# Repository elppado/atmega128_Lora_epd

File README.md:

# Atmega128_Lora_epd  wire-less Chat
## [ LoRa와 ePaper를 사용한 AVR 기반 저전력 다용도 통신 단말 ]

### 🚀 프로젝트 소개
------
atmega128과 Lora 모듈, 전자잉크 디스플레이를 사용하여 무선 채팅기 개발

### 🕰️ 개발 기간
------
* 22.07 ~ 22.09

### 📋 개발내용
------
- [Schematic](https://github.com/elppado/atmega128_Lora_epd/tree/main/PCB)
- [F/W](https://github.com/elppado/atmega128_Lora_epd/tree/main/firmware)  

### ⚙️ 개발환경
-----
* C
* **Tool** : xcode(avrdude_cross compile), kicad, fusion360

### 📋 BOM
------
Lora : NMT-UD434R0

Display : 2.13 inch EInk e-paper Display 250*122

Keypad : Q10

This project is licensed under the terms of the MIT license.

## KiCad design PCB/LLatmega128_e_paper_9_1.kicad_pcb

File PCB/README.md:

# PCB
-------

- atmega128a
- LoRa Module
- e-ink display

### Schematic

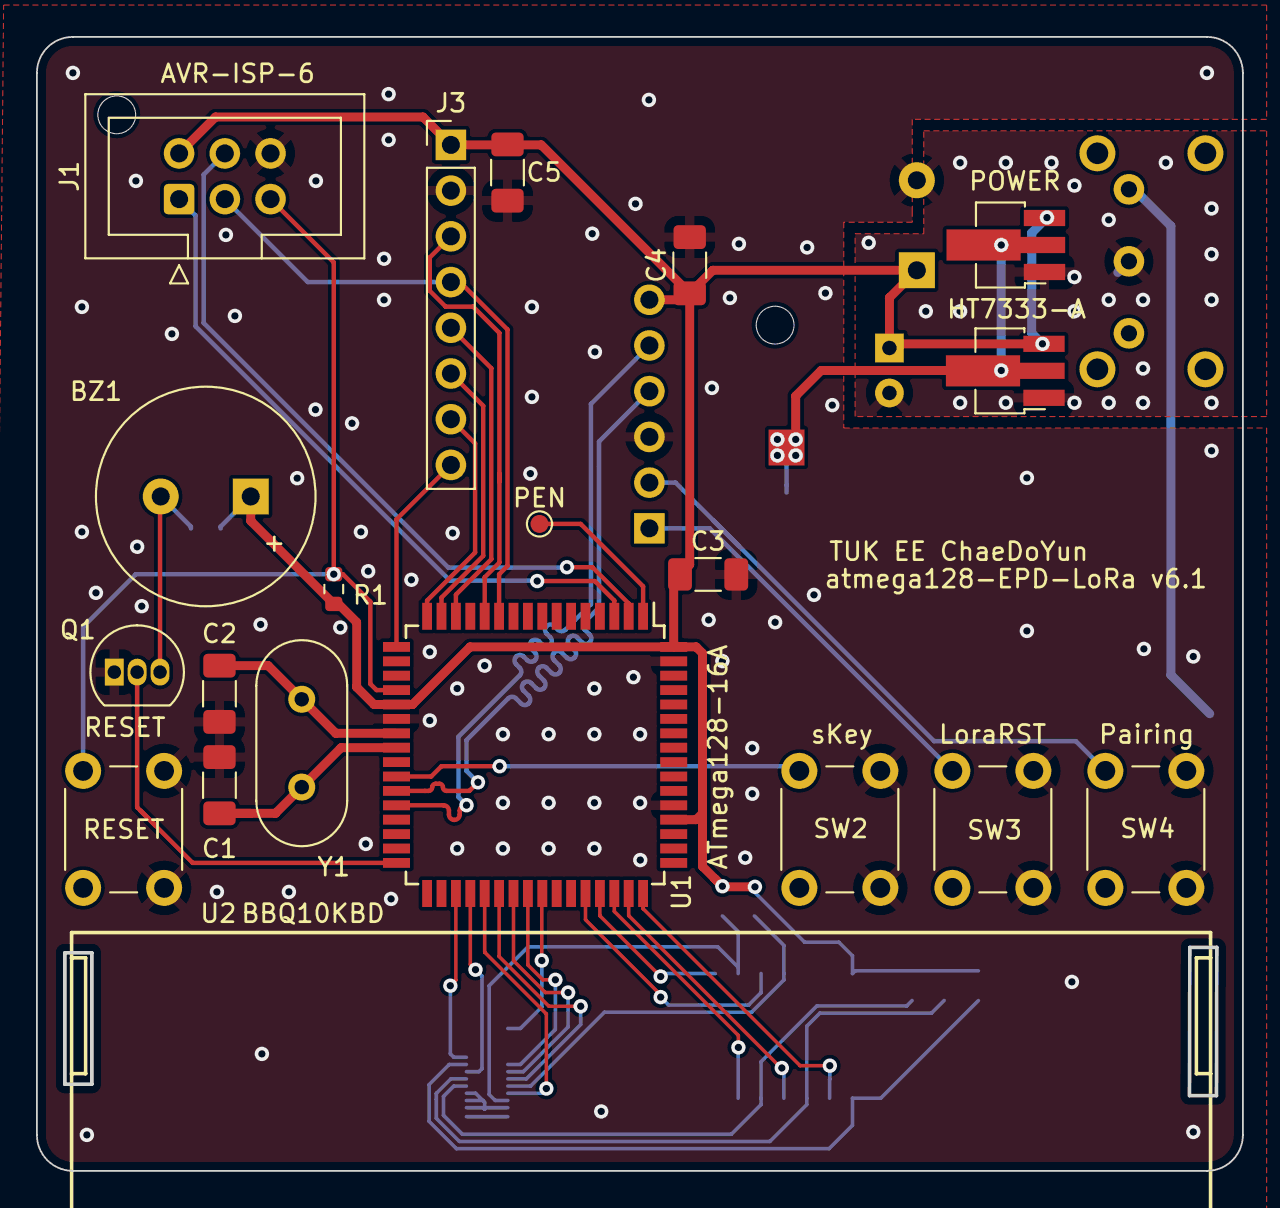
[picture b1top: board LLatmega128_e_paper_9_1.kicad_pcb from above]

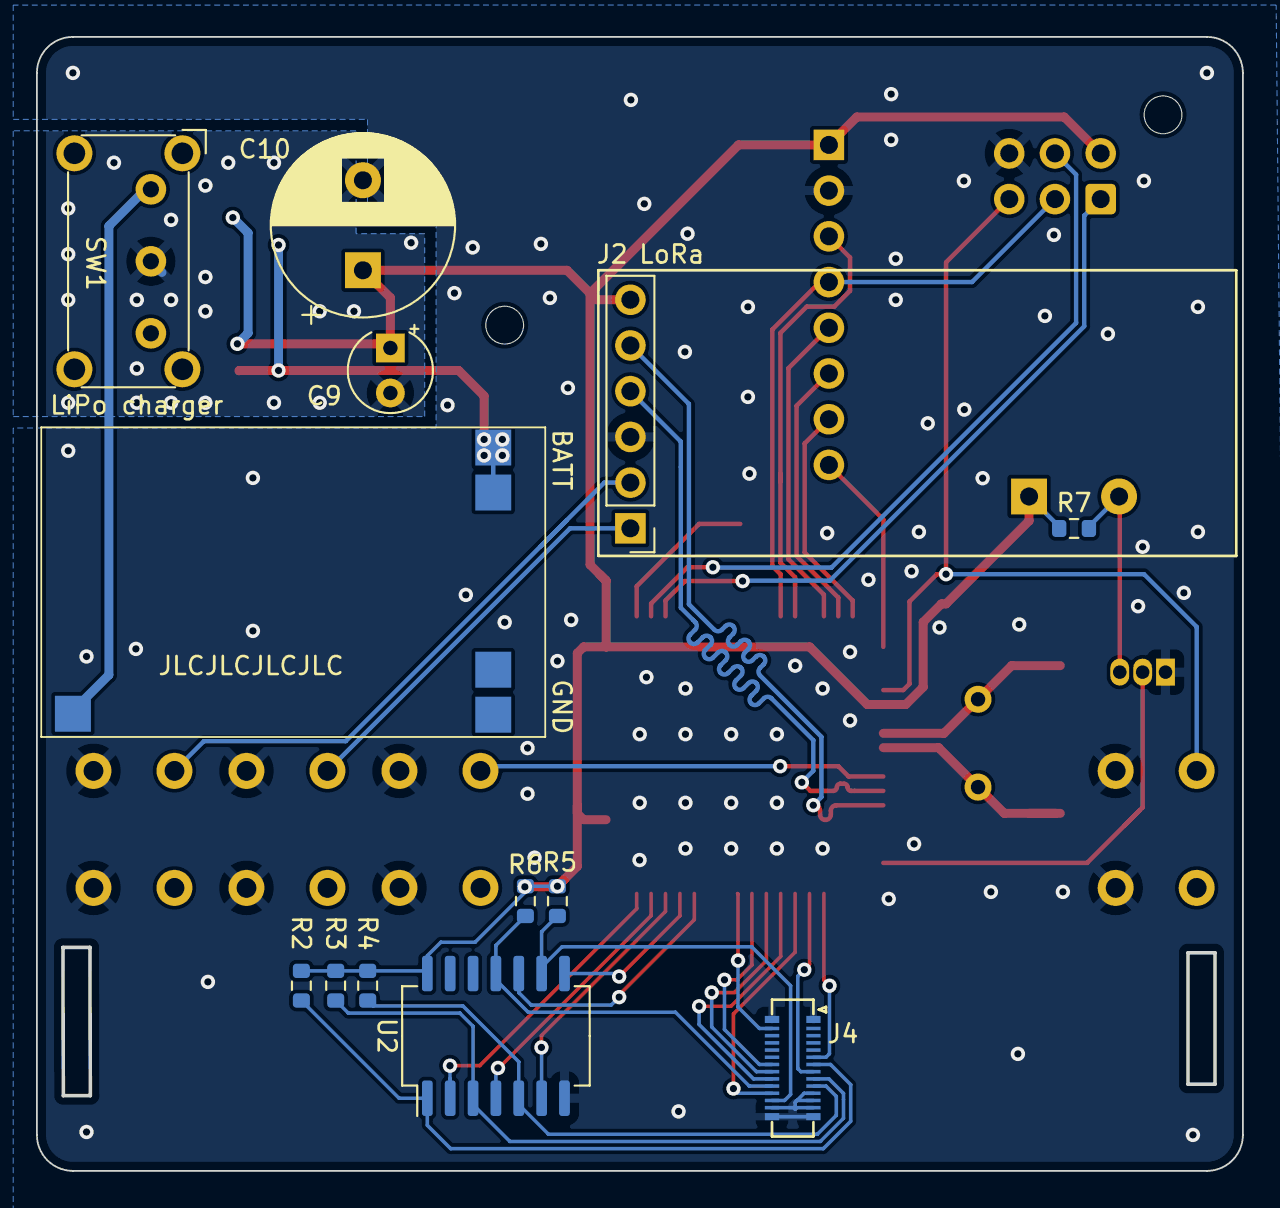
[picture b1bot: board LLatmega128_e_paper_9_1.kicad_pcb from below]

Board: 2 copper layers, 66.9 x 62.9 mm, 32 parts (12 on the bottom side), 38 nets.

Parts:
BZ1: Buzzer; Buzzer_12x9.5RM7.6
C1, C2: C22pF; C_1206_3216Metric_Pad1.33x1.80mm_HandSolder
C3, C4, C5: C_1206_3216Metric_Pad1.33x1.80mm_HandSolder
C9: CP_Radial_Tantal_D4.5mm_P2.50mm
C10: CP_Radial_D10.0mm_P5.00mm
J1: AVR-ISP-6; IDC-Header_2x03_P2.54mm_Vertical
J2: Conn_01x06_Male; PinHeader_1x06_P2.54mm_Vertical
J3: ePaper; PinHeader_1x08_P2.54mm_Vertical
J4: Conn_02x14_Counter_Clockwise; Hirose_BM14-24DS-2DSA_2x14_P2.00mm_Vertical
L1, L1#2: HT7333-A; SOT-89-3_Handsoldering
PEN: TestPoint_Pad_D1.0mm
POWER: SW_E-Switch_EG1224_SPDT_Angled
Q1: PN2222A; TO-92_Inline
R1: R10k; R_0603_1608Metric
R2, R3, R4, R5, R6, R7: R; R_0603_1608Metric
SW1, SW2, SW3, SW4: SW_Push; SW_PUSH_6mm_H4.3mm
U1: ATmega128-16A; TQFP-64_14x14mm_P0.8mm
U2: BBQ10KBD; Reverb_BTDR-1A
U2#2: 74HC14; SO-14_5.3x10.2mm_P1.27mm
Y1: Crystal; Crystal_HC49-4H_Vertical

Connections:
+3V3: BZ1.1 (-), C3.1, C4.1, C5.1, C9.1, C10.1, J1.2 (VCC), J2.6, J3.1, L1.3 (VOUT), L1#2.3 (VOUT), R1.1, R2.1, R3.1, R4.1, R5.1, R6.1, R7.1, U1.21 (VCC), U1.52 (VCC), U1.64 (AVCC), U2#2.14 (VCC)
-BATT: L1.2 (VIN), L1#2.2 (VIN)
/BUSY: J3.8, U1.17 (PB7)
/BUZZ: Q1.2 (B), U1.32 (PD7)
/COL1: U1.48 (PA3), U2#2.2
/COL2: U1.47 (PA4), U2#2.4
/COL3: U1.46 (PA5), U2#2.6
/COL4: U1.45 (PA6), U2#2.8
/COL5: U1.44 (PA7), U2#2.10
/CS: J3.5, U1.14 (PB4)
/D/C: J3.6, U1.15 (PB5)
/KCOL1: J4.7, R2.2, U2#2.1
/KCOL2: J4.9, R3.2, U2#2.3
/KCOL3: J4.10, R4.2, U2#2.5
/KCOL4: J4.17, R5.2, U2#2.9
/KCOL5: J4.19, R6.2, U2#2.11
/LoraRST: J2.1, SW3.2
/PIO6: J2.2, SW4.2
/RES: J3.7, U1.16 (PB6)
/ROW1: J4.6, U1.35 (PC0)
/ROW2: J4.8, U1.36 (PC1)
/ROW3: J4.18, U1.37 (PC2)
/ROW4: J4.20, U1.38 (PC3)
/ROW5: J4.21, U1.39 (PC4)
/ROW6: J4.22, U1.40 (PC5)
/ROW7: J4.27, U1.41 (PC6)
/RST: J1.5 (~RST), R1.2, SW1.2, U1.20 (~RESET)
/RXD0: J1.4 (MOSI), U1.2 (PE0)
/RXD1: J2.4, U1.27 (PD2)
/SCK: J1.3 (SCK), J3.4, U1.11 (PB1)
/SDI: J3.3, U1.12 (PB2)
/TXD0: J1.1 (MISO), U1.3 (PE1)
/TXD1: J2.5, U1.28 (PD3)
/X1: C1.2, U1.24 (XTAL1), Y1.2
/X2: C2.1, U1.23 (XTAL2), Y1.1
/sKEY: SW2.2, U1.26 (PD1)
GND: C1.1, C2.2, C3.2, C4.2, C5.2, C9.2, C10.2, J1.6 (GND), J2.3, J3.2, J4.1, J4.4, J4.5, J4.11, J4.12, J4.13, J4.14, J4.15, J4.16, J4.28, L1.1 (GND), L1#2.1 (GND), POWER.2, Q1.1 (E), SW1.1, SW2.1, SW3.1, SW4.1, U1.22 (GND), U1.53 (GND), U1.63 (GND), U2#2.7 (GND)
unnamed: BZ1.2 (+), Q1.3 (C), R7.2

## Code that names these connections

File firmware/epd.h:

/*
 * epd.h
 *
 * Created: 2022-07-17 오후 1:14:07
 *  Author: chaedoyun
 */ 


#ifndef EPD_H_
#define EPD_H_


#define SCK_Pin PB1
#define SDI_Pin PB2
#define CS_Pin PB4
#define DC_Pin PB5
#define RES_Pin PB6
#define BUSY PB7


#define EPD_W21_MOSI_0	PORTB &= ~( 1<< SDI_Pin)
#define EPD_W21_MOSI_1	PORTB |= ( 1<< SDI_Pin)

#define EPD_W21_CLK_0	PORTB &= ~( 1<< SCK_Pin)
#define EPD_W21_CLK_1	PORTB |= ( 1<< SCK_Pin)

#define EPD_W21_CS_0	PORTB &= ~( 1<< CS_Pin)
#define EPD_W21_CS_1	PORTB |= ( 1<< CS_Pin)

#define EPD_W21_DC_0	PORTB &= ~( 1<< DC_Pin)
#define EPD_W21_DC_1	PORTB |= ( 1<< DC_Pin)

#define EPD_W21_RST_0	PORTB &= ~( 1<< RES_Pin)
#define EPD_W21_RST_1	PORTB |= ( 1<< RES_Pin)


//250*122///////////////////////////////////////


#define MAX_LINE_BYTES 16// =128/8
#define MAX_COLUMN_BYTES  250

#define ALLSCREEN_GRAGHBYTES  4000





////////FUNCTION//////
void driver_delay_us(unsigned int xus);
void driver_delay(unsigned long xms);
void SPI_Delay(unsigned char xrate);


//EPD
void Epaper_READBUSY(void);
void SPI_Write(unsigned char value);
void Epaper_Write_Command(unsigned char cmd);
void Epaper_Write_Data(unsigned char datas);

void EPD_HW_Init(void); //Electronic paper initialization
void EPD_Part_Init(void); //Local refresh initialization

void EPD_Part_Update(void);
void EPD_Update(void);

void EPD_WhiteScreen_Black(void);
void EPD_WhiteScreen_White(void);
void EPD_DeepSleep(void);
//Display
void EPD_WhiteScreen_ALL(const unsigned char * datas);
void EPD_SetRAMValue_BaseMap(const unsigned char * datas);
void EPD_Dis_Part(unsigned int x_start,unsigned int y_start,const unsigned char * datas,unsigned int PART_COLUMN,unsigned int PART_LINE);





void driver_delay_us(unsigned int xus)  //1us
{
	for(;xus>1;xus--);
}//us delay


void driver_delay(unsigned long xms) //1ms
{
	unsigned long i = 0 , j=0;

	for(j=0;j<xms;j++)
	{
		for(i=0; i<256; i++);
	}
}



void EPD_WhiteScreen_ALL(const unsigned char * datas)
{
   unsigned int i;
    Epaper_Write_Command(0x24);   //write RAM for black(0)/white (1)
   for(i=0;i<ALLSCREEN_GRAGHBYTES;i++)
   {
     Epaper_Write_Data(pgm_read_byte(&datas[i]));
   }
   EPD_Update();
}




//////////////////////SPI///////////////////////////////////
void SPI_Delay(unsigned char xrate)
{
	unsigned char i;
	while(xrate)
	{
		for(i=0;i<2;i++);
		xrate--;
		
	}
}


void SPI_Write(unsigned char value)
{
	unsigned char i;
	SPI_Delay(1);
	for(i=0; i<8; i++)
	{
		EPD_W21_CLK_0;
		SPI_Delay(1);
		if(value & 0x80)
		EPD_W21_MOSI_1;
		else
		EPD_W21_MOSI_0;
		value = (value << 1);
		SPI_Delay(1);
		driver_delay_us(1);
		EPD_W21_CLK_1;
		SPI_Delay(1);
	}
}


void Epaper_Write_Command(unsigned char cmd)
{
	SPI_Delay(1);
	EPD_W21_CS_0;
	EPD_W21_DC_0;   // command write
	SPI_Write(cmd);
	EPD_W21_CS_1;
}
void Epaper_Write_Data(unsigned char datas)
{
	SPI_Delay(1);
	EPD_W21_CS_0;
	EPD_W21_DC_1;   // data write
	SPI_Write(datas);
	EPD_W21_CS_1;
}

/////////////////EPD settings Functions/////////////////////
//////////////////////////////////////////////////////////////////////////////////////////////////
//SSD1680
void EPD_HW_Init(void){
    
    EPD_W21_RST_0;  // Module reset
    _delay_ms(10); //At least 10ms delay
    EPD_W21_RST_1;
    _delay_ms(10); //At least 10ms delay

    Epaper_READBUSY();
    Epaper_Write_Command(0x12);  //SWRESET
    Epaper_READBUSY();
       
     Epaper_Write_Command(0x01); //Driver output control
     Epaper_Write_Data(0xF9);
     Epaper_Write_Data(0x00);
     Epaper_Write_Data(0x00);

     Epaper_Write_Command(0x11); //data entry mode
     Epaper_Write_Data(0x01);

     Epaper_Write_Command(0x44); //set Ram-X address start/end position
     Epaper_Write_Data(0x00);
     Epaper_Write_Data(0x0F);    //0x0F-->(15+1)*8=128

     Epaper_Write_Command(0x45); //set Ram-Y address start/end position
     Epaper_Write_Data(0xF9);   //0xF9-->(249+1)=250
     Epaper_Write_Data(0x00);
     Epaper_Write_Data(0x00);
     Epaper_Write_Data(0x00);

     Epaper_Write_Command(0x3C); //BorderWavefrom
     Epaper_Write_Data(0x05);
         
     Epaper_Write_Command(0x21); //  Display update control
     Epaper_Write_Data(0x00);
     Epaper_Write_Data(0x80);
         
     Epaper_Write_Command(0x18); //Read built-in temperature sensor
     Epaper_Write_Data(0x80);

     Epaper_Write_Command(0x4E);   // set RAM x address count to 0;
     Epaper_Write_Data(0x00);
     Epaper_Write_Command(0x4F);   // set RAM y address count to 0X199;
     Epaper_Write_Data(0xF9);
     Epaper_Write_Data(0x00);
     Epaper_READBUSY();
}

/*
//////////////////////////////All screen update////////////////////////////////////////////
void EPD_WhiteScreen_ALL(const unsigned char * datas)
{
	unsigned int i;
	Epaper_Write_Command(0x24);   //write RAM for black(0)/white (1)
	for(i=0;i<ALLSCREEN_GRAGHBYTES;i++)
	{
		Epaper_Write_Data(pgm_read_byte(&datas[i]));
	}
	EPD_Update();
}
*/
/////////////////////////////////////////////////////////////////////////////////////////

void EPD_Update(void)
{
	Epaper_Write_Command(0x22); //Display Update Control
	Epaper_Write_Data(0xF7);
	Epaper_Write_Command(0x20); //Activate Display Update Sequence
	Epaper_READBUSY();

}
void EPD_Part_Update(void)
{
	Epaper_Write_Command(0x22); //Display Update Control
	Epaper_Write_Data(0xFF);
	Epaper_Write_Command(0x20); //Activate Display Update Sequence
	Epaper_READBUSY();
}
void EPD_DeepSleep(void)
{
	Epaper_Write_Command(0x10); //enter deep sleep
	Epaper_Write_Data(0x01);
    //Epaper_READBUSY();
    _delay_ms(100);
}
void Epaper_READBUSY(void)
{
    while(PINB & 0x80);

}
///////////////////////////Part update//////////////////////////////////////////////
void EPD_SetRAMValue_BaseMap( const unsigned char * datas)
{
	unsigned int i;
	const unsigned char  *datas_flag;
	datas_flag=datas;

	Epaper_Write_Command(0x24);   //Write Black and White image to RAM

	for(i=0;i<ALLSCREEN_GRAGHBYTES;i++){
        
		Epaper_Write_Data(pgm_read_byte(&datas[i]));
	}

	datas=datas_flag;

	Epaper_Write_Command(0x26);   //Write Black and White image to RAM

	for(i=0;i<ALLSCREEN_GRAGHBYTES;i++)
	{
		Epaper_Write_Data(pgm_read_byte(&datas[i]));
	}

	EPD_Update();
}

void EPD_Dis_Part(unsigned int x_start,unsigned int y_start,const unsigned char * datas,unsigned int PART_COLUMN,unsigned int PART_LINE)
{
    unsigned int i;
      unsigned int x_end,y_start1,y_start2,y_end1,y_end2;
      x_start=x_start/8;//
      x_end=x_start+PART_LINE/8-1;
      
      y_start1=0;
      y_start2=y_start;
      if(y_start>=256)
      {
        y_start1=y_start2/256;
        y_start2=y_start2%256;
      }
      y_end1=0;
      y_end2=y_start+PART_COLUMN-1;
      if(y_end2>=256)
      {
        y_end1=y_end2/256;
        y_end2=y_end2%256;
      }
      //Reset
      EPD_W21_RST_0;  // Module reset
      _delay_ms(10);//At least 10ms delay
      EPD_W21_RST_1;
      _delay_ms(10); //At least 10ms delay
        
      Epaper_Write_Command(0x3C); //BorderWavefrom
      Epaper_Write_Data(0x80);
 
      Epaper_Write_Command(0x44);       // set RAM x address start/end, in page 35
      Epaper_Write_Data(x_start);    // RAM x address start at 00h;
      Epaper_Write_Data(x_end);    // RAM x address end at 0fh(15+1)*8->128
      Epaper_Write_Command(0x45);       // set RAM y address start/end, in page 35
      Epaper_Write_Data(y_start2);    // RAM y address start at 0127h;
      Epaper_Write_Data(y_start1);    // RAM y address start at 0127h;
      Epaper_Write_Data(y_end2);    // RAM y address end at 00h;
      Epaper_Write_Data(y_end1);    // ????=0


      Epaper_Write_Command(0x4E);   // set RAM x address count to 0;
      Epaper_Write_Data(x_start);
      Epaper_Write_Command(0x4F);   // set RAM y address count to 0X127;
      Epaper_Write_Data(y_start2);
      Epaper_Write_Data(y_start1);
      
      
       Epaper_Write_Command(0x24);   //Write Black and White image to RAM
       for(i=0;i<PART_COLUMN*PART_LINE/8;i++)
       {
         Epaper_Write_Data(pgm_read_byte(&datas[i]));
       }
       EPD_Part_Update();


}




/////////////////////////////////Single display////////////////////////////////////////////////

void EPD_WhiteScreen_White(void)

{
	unsigned int i,k;
	Epaper_Write_Command(0x24);   //write RAM for black(0)/white (1)
	for(k=0;k<250;k++)
	{
		for(i=0;i<16;i++)
		{
			Epaper_Write_Data(0xff);
		}
	}
	EPD_Update();
}


#endif /* EPD_H_ */

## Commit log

2022-09-26 emmb 제출 테스트 중...
2022-09-26 full tested !!
2022-09-26 full tested!
2022-10-03 full tested
2022-10-03 tested
2023-07-26 edit & update
2023-11-11 remove
2023-11-11 .gitignore 생성
